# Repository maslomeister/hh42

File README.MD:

# hh42

Беспроводная эрго сплит клавиатура заточенная под руки владельца репозитория, MX LP и [ZMK](https://zmk.dev/).

Спасибо [Corne](https://github.com/foostan/crkbd) за вдохновление.

# Гербер файлы

Скачать гербер файлы ПЦБ можно [ТУТ](https://github.com/maslomeister/hh42/blob/main/pcb/production/hh42.zip)

# Стоимость сборки

| Предмет                 | Цена в $                                                                                        | Комментарий             | Ссылка                                                                                                                              |
| ----------------------- | ----------------------------------------------------------------------------------------------- | ----------------------- | ----------------------------------------------------------------------------------------------------------------------------------- |
| ПЦБ                     | 25                                                                                              | Цена за 5 комплектов    | https://aliexpress.ru/item/1005006573905744.html                                                                                    |
| MX LP свитчи            | 27                                                                                              | Цена за 60 штук         | https://aliexpress.ru/item/1005006328228130.html                                                                                    |
| Ножки                   | 4.6                                                                                             | Цена за 100 штук        | https://aliexpress.ru/item/32963141746.html                                                                                         |
| SuperMini               | 4.8                                                                                             | Клон nice nano 2.0      | https://aliexpress.ru/item/1005006035267231.html                                                                                    |
| Диоды                   | 0.85                                                                                            | Цена за 100 штук        | https://aliexpress.ru/item/32849879904.html                                                                                         |
| PCM12SMTR переключатель | 4                                                                                               | Цена за 5 штук          | https://aliexpress.ru/item/1005005366298406.html                                                                                    |
| Reset кнопка            | 1.5                                                                                             | 4.3ММ; Цена за 100 штук | https://aliexpress.ru/item/32882161197.html                                                                                         |
| Сокеты для контроллера  | 1.9                                                                                             | Цена за 100 штук        | https://aliexpress.ru/item/32980406694.html                                                                                         |
| Пины для контроллера    | 4.3                                                                                             | Цена за 100 штук        | https://aliexpress.ru/item/32858430771.html                                                                                         |
| Аккумулятор 110 mah     | 4.2                                                                                             | -                       | https://www.ozon.ru/product/akkumulyator-dlya-videoregistratora-akb-batareya-3-7v-130mah-5x12x30-li-pol-2-provoda-501230-1047383524 |
| Итог за 1 клавиатуру    | <!--5+27+4.6/100*30+4/8+4/8+0.85/100*42+4/5*2+1.5/10*2+1.9/100*48+4.3/100*48+4.2+4.2--> **~48** |

# Прошивка и раскладка

Готовые файлы прошивки [ТУТ](https://github.com/maslomeister/hh42/tree/main/firmwares), репозиторий с исходниками [ТУТ](https://github.com/maslomeister/zmk-configs)

### Основной слой

### Lower слой

### Raise слой

### Combined слой (Lower+Raise)

# Сборка

Контроллеры паяются диодами вверх, все остальное видно на шелкографии. Аккумулятор на 110 mah паять к пинам под контроллерами чтобы питание можно было отключать через переключатель.

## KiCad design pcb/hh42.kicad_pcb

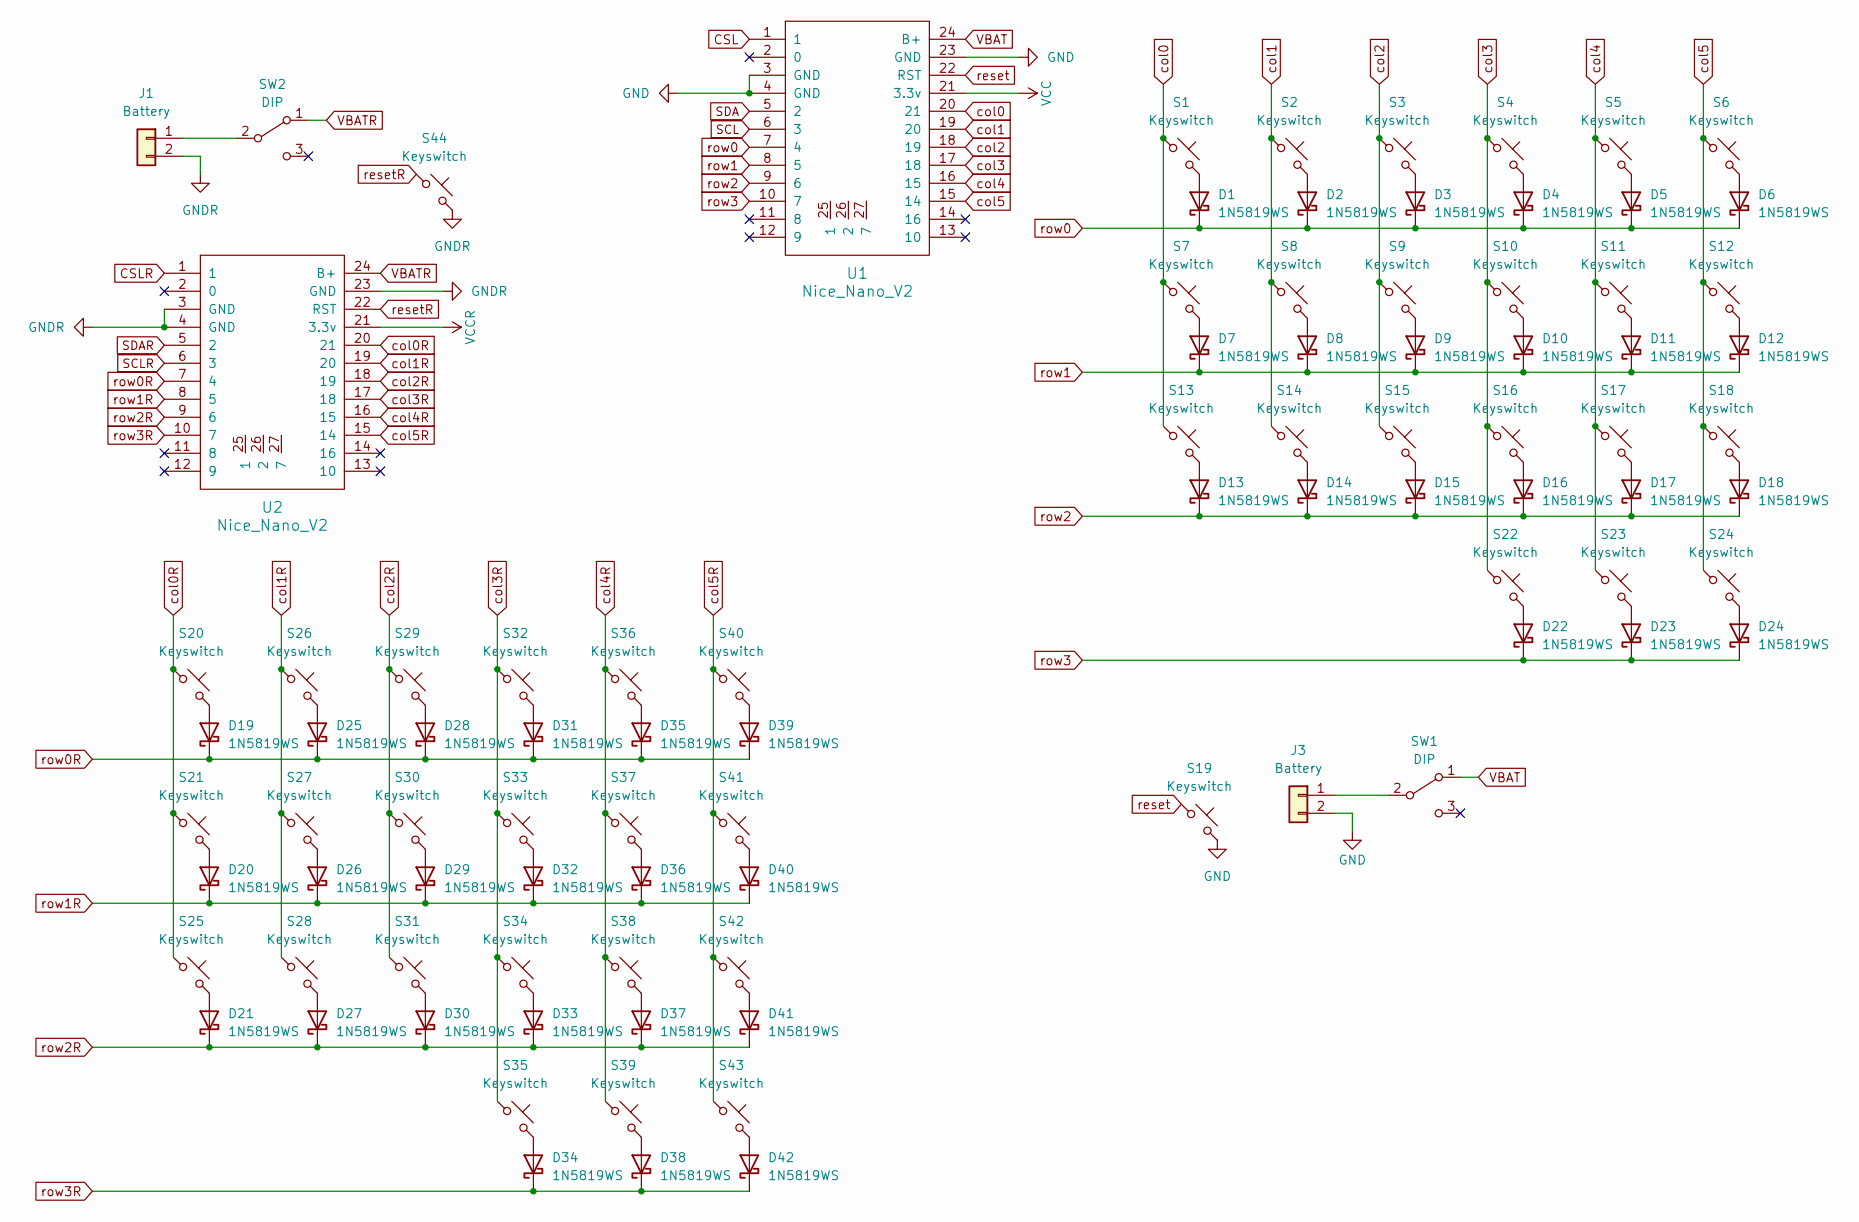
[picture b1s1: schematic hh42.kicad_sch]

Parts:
D1, D2, D3, D4, D5, D6, D7, D8, D9, D10, D11, D12, D13, D14, D15, D16, D17, D18, D19, D20, D21, D22, D23, D24, D25, D26, D27, D28, D29, D30, D31, D32, D33, D34, D35, D36, D37, D38, D39, D40, D41, D42: 1N5819WS; D_SOD123
J1, J3: Battery; PinHeader_1x02_P2.54mm_Vertical
S1, S2, S3, S4, S5, S6, S7, S8, S9, S10, S11, S12, S13, S14, S15, S16, S17, S18, S20, S21, S22, S23, S24, S25, S26, S27, S28, S29, S30, S31, S32, S33, S34, S35, S36, S37, S38, S39, S40, S41, S42, S43: Keyswitch; MXLP
S19, S44: Keyswitch; ResetSW
SW1, SW2: DIP; SW_SPDT_PCM12; LCSC Part Number C221841
U1, U2: Nice_Nano_V2

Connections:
CSL: U1.1
CSLR: U2.1
GND: J3.2, S19.2, U1.3 (GND), U1.4 (GND), U1.23 (GND)
GNDR: J1.2, S44.2, U2.3 (GND), U2.4 (GND), U2.23 (GND)
unnamed: D1.2 (A), S1.2
unnamed: D2.2 (A), S2.2
unnamed: D3.2 (A), S3.2
unnamed: D4.2 (A), S4.2
unnamed: D5.2 (A), S5.2
unnamed: D6.2 (A), S6.2
unnamed: D7.2 (A), S7.2
unnamed: D8.2 (A), S8.2
unnamed: D9.2 (A), S9.2
unnamed: D10.2 (A), S10.2
unnamed: D11.2 (A), S11.2
unnamed: D12.2 (A), S12.2
unnamed: D13.2 (A), S13.2
unnamed: D14.2 (A), S14.2
unnamed: D15.2 (A), S15.2
unnamed: D16.2 (A), S16.2
unnamed: D17.2 (A), S17.2
unnamed: D18.2 (A), S18.2
unnamed: D19.2 (A), S20.2
unnamed: D20.2 (A), S21.2
unnamed: D21.2 (A), S25.2
unnamed: D22.2 (A), S22.2
unnamed: D23.2 (A), S23.2
unnamed: D24.2 (A), S24.2
unnamed: D25.2 (A), S26.2
unnamed: D26.2 (A), S27.2
unnamed: D27.2 (A), S28.2
unnamed: D28.2 (A), S29.2
unnamed: D29.2 (A), S30.2
unnamed: D30.2 (A), S31.2
unnamed: D31.2 (A), S32.2
unnamed: D32.2 (A), S33.2
unnamed: D33.2 (A), S34.2
unnamed: D34.2 (A), S35.2
unnamed: D35.2 (A), S36.2
unnamed: D36.2 (A), S37.2
unnamed: D37.2 (A), S38.2
unnamed: D38.2 (A), S39.2
unnamed: D39.2 (A), S40.2
unnamed: D40.2 (A), S41.2
unnamed: D41.2 (A), S42.2
unnamed: D42.2 (A), S43.2
unnamed: J1.1, SW2.2 (B)
unnamed: J3.1, SW1.2 (B)
SCL: U1.6 (3)
SCLR: U2.6 (3)
SDA: U1.5 (2)
SDAR: U2.5 (2)
VBAT: SW1.1 (A), U1.24 (B+)
VBATR: SW2.1 (A), U2.24 (B+)
VCC: U1.21 (3.3v)
VCCR: U2.21 (3.3v)
col0: S1.1, S7.1, S13.1, U1.20 (21)
col0R: S20.1, S21.1, S25.1, U2.20 (21)
col1: S2.1, S8.1, S14.1, U1.19 (20)
col1R: S26.1, S27.1, S28.1, U2.19 (20)
col2: S3.1, S9.1, S15.1, U1.18 (19)
col2R: S29.1, S30.1, S31.1, U2.18 (19)
col3: S4.1, S10.1, S16.1, S22.1, U1.17 (18)
col3R: S32.1, S33.1, S34.1, S35.1, U2.17 (18)
col4: S5.1, S11.1, S17.1, S23.1, U1.16 (15)
col4R: S36.1, S37.1, S38.1, S39.1, U2.16 (15)
col5: S6.1, S12.1, S18.1, S24.1, U1.15 (14)
col5R: S40.1, S41.1, S42.1, S43.1, U2.15 (14)
reset: S19.1, U1.22 (RST)
resetR: S44.1, U2.22 (RST)
row0: D1.1 (K), D2.1 (K), D3.1 (K), D4.1 (K), D5.1 (K), D6.1 (K), U1.7 (4)
row0R: D19.1 (K), D25.1 (K), D28.1 (K), D31.1 (K), D35.1 (K), D39.1 (K), U2.7 (4)
row1: D7.1 (K), D8.1 (K), D9.1 (K), D10.1 (K), D11.1 (K), D12.1 (K), U1.8 (5)
row1R: D20.1 (K), D26.1 (K), D29.1 (K), D32.1 (K), D36.1 (K), D40.1 (K), U2.8 (5)
row2: D13.1 (K), D14.1 (K), D15.1 (K), D16.1 (K), D17.1 (K), D18.1 (K), U1.9 (6)
row2R: D21.1 (K), D27.1 (K), D30.1 (K), D33.1 (K), D37.1 (K), D41.1 (K), U2.9 (6)
row3: D22.1 (K), D23.1 (K), D24.1 (K), U1.10 (7)
row3R: D34.1 (K), D38.1 (K), D42.1 (K), U2.10 (7)

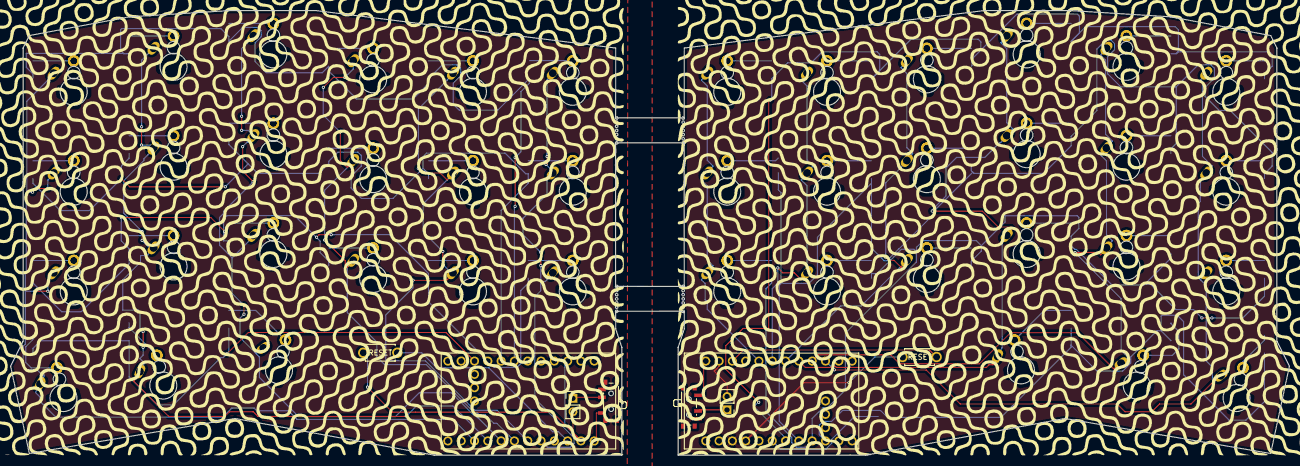
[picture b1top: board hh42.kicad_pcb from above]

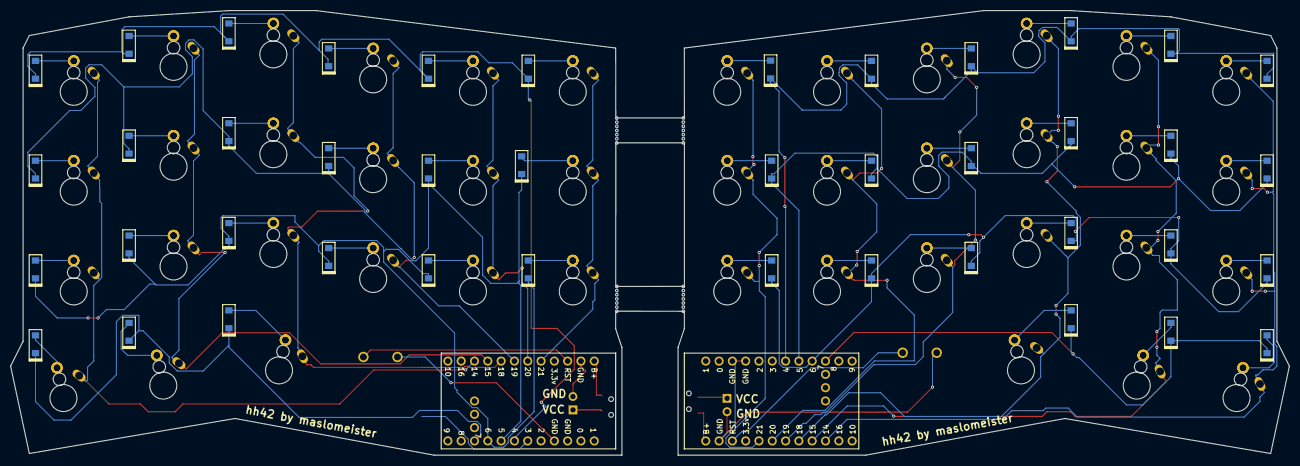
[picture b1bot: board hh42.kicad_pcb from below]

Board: 2 copper layers, 244.1 x 84.9 mm, 98 parts (42 on the bottom side), 70 nets.

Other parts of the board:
FOREGROUNDL: LOGO; silkscreen_art_inverted
FOREGROUNDR: LOGO; silkscreen_art_inverted
lBT4, lBT42: Breakaway Tabs; Breakaway_Tabs
rBT4, rBT42: Breakaway Tabs; Breakaway_Tabs

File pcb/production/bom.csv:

Designator,Footprint,Quantity,Value,LCSC Part #
"D1, D10, D11, D12, D13, D14, D15, D16, D17, D18, D19, D2, D20, D21, D22, D23, D24, D25, D26, D27, D28, D29, D3, D30, D31, D32, D33, D34, D35, D36, D37, D38, D39, D4, D40, D41, D42, D5, D6, D7, D8, D9",D_SOD123,42,1N5819WS,
"J1, J3",PinHeader_1x02_P2.54mm_Vertical,2,Battery,
"S1, S10, S11, S12, S13, S14, S15, S16, S17, S18, S2, S20, S21, S22, S23, S24, S25, S26, S27, S28, S29, S3, S30, S31, S32, S33, S34, S35, S36, S37, S38, S39, S4, S40, S41, S42, S43, S5, S6, S7, S8, S9",MXLP,42,Keyswitch,
"S19, S44",ResetSW,2,Keyswitch,
"SW1, SW2",SW_SPDT_PCM12,2,DIP,
"U1, U2",Nice_Nano_V2,2,Nice_Nano_V2,

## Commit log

2024-04-24 init
2024-04-24 proper urls
2024-04-24 cleanup
2024-04-24 add gerber files
2024-04-24 Add controller mounts and battery
2024-04-24 Добавил сокеты и пины в стоимость
2024-05-08 new firmware
2024-05-15 add deep sleep
2024-07-23 new keyboard image
